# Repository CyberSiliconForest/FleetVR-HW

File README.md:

# FleetVR Hardware Design
## Abstract

## License
Most hardware designes are released under CERN OHL S v2.

Refer REUSE description for further information

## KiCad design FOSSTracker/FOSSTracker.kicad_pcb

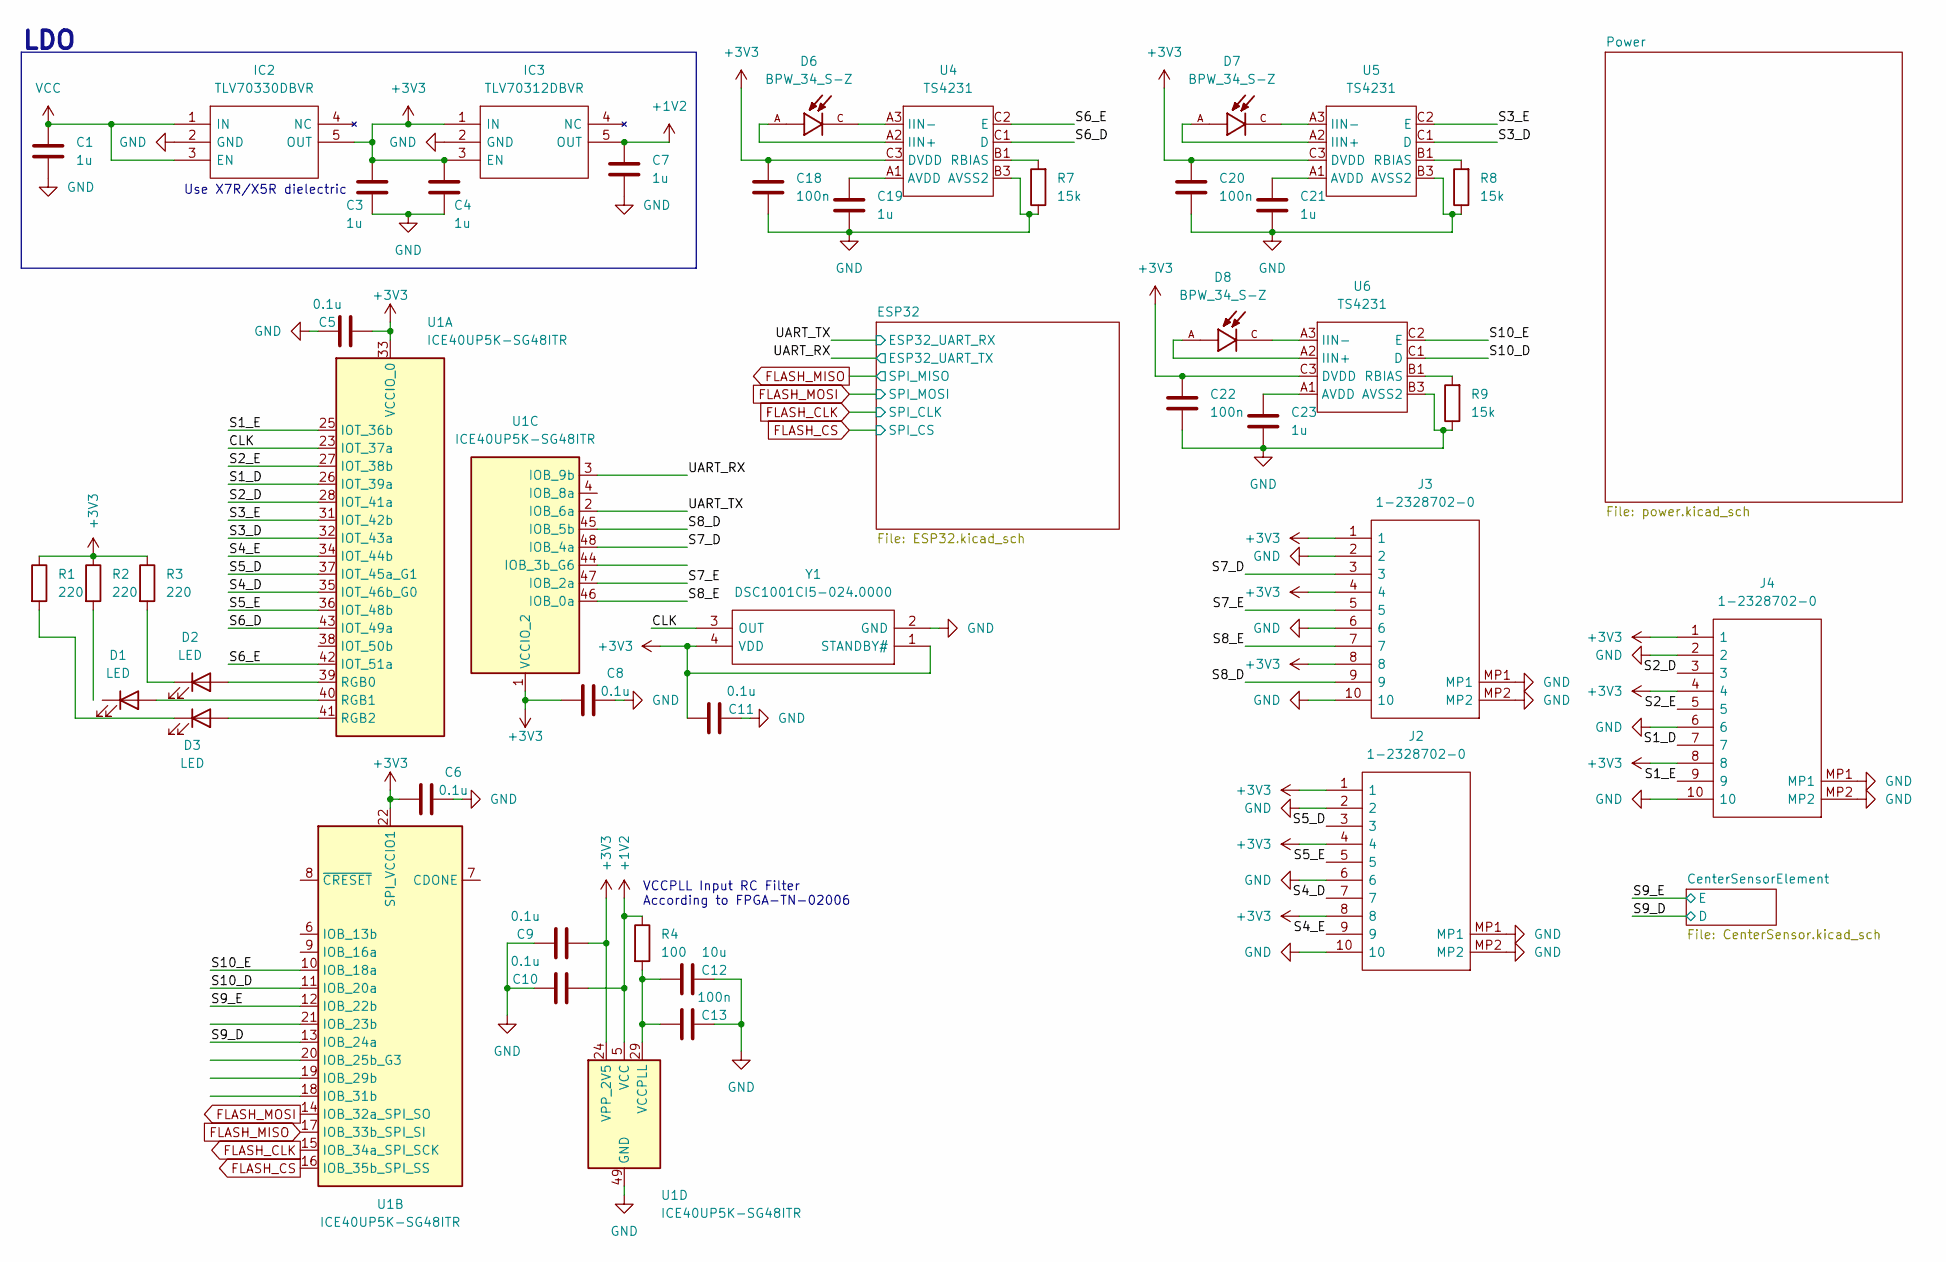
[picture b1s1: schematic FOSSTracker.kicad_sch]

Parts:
C1, C3, C4, C7, C19, C21, C23: 1u; C_0603_1608Metric
C5, C6, C8, C9, C10, C11: 0.1u; C_0603_1608Metric
C12: 10u; C_0603_1608Metric
C13, C18, C20, C22: 100n; C_0603_1608Metric
D1, D2, D3: LED; LED_0805_2012Metric_Pad1.15x1.40mm_HandSolder
D6, D7, D8: BPW_34_S-Z; DIO_BPW_34_S-Z; PARTREV 1.5
IC2: TLV70330DBVR; SOT95P280X145-5N; Mouser Part Number 595-TLV70330DBVR
IC3: TLV70312DBVR; SOT95P280X145-5N; Mouser Part Number 595-TLV70312DBVR
J2, J3, J4: 1-2328702-0; 123287020; Mouser Part Number 571-1-2328702-0
R1, R2, R3: 220; R_0603_1608Metric
R4: 100; R_0603_1608Metric
R7, R8, R9: 15k; R_0603_1608Metric
U1: ICE40UP5K-SG48ITR; QFN-48-1EP_7x7mm_P0.5mm_EP5.6x5.6mm
U4, U5, U6: TS4231; TS4231 WLCSP9
Y1: DSC1001CI5-024.0000; DSC1001CI50240000; Mouser Part Number 998-1001CI5-024.0000

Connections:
+1V2: C7.1, C10.1, IC3.5 (OUT), R4.1, U1.5 (VCC), U1.30 (VCC)
+3V3: C3.1, C4.1, C5.1, C6.1, C8.1, C9.1, C11.2, C18.1, C20.1, C22.1, IC2.5 (OUT), IC3.1 (IN), IC3.3 (EN), J2.1, J2.4, J2.8, J3.1, J3.4, J3.8, J4.1, J4.4, J4.8, R1.1, R2.1, R3.1, U1.1 (VCCIO_2), U1.22 (SPI_VCCIO1), U1.24 (VPP_2V5), U1.33 (VCCIO_0), U4.C3 (DVDD), U5.C3 (DVDD), U6.C3 (DVDD), Y1.1 (STANDBY#), Y1.4 (VDD); also elsewhere on the board
/CLK: U1.23 (IOT_37a), Y1.3 (OUT)
/S1_D: J4.7, U1.26 (IOT_39a)
/S1_E: J4.9, U1.25 (IOT_36b)
/S2_D: J4.3, U1.28 (IOT_41a)
/S2_E: J4.5, U1.27 (IOT_38b)
/S3_D: U1.32 (IOT_43a), U5.C1 (D)
/S3_E: U1.31 (IOT_42b), U5.C2 (E)
/S4_D: J2.7, U1.35 (IOT_46b_G0)
/S4_E: J2.9, U1.34 (IOT_44b)
/S5_D: J2.3, U1.37 (IOT_45a_G1)
/S5_E: J2.5, U1.36 (IOT_48b)
/S6_D: U1.43 (IOT_49a), U4.C1 (D)
/S6_E: U1.42 (IOT_51a), U4.C2 (E)
/S7_D: J3.3, U1.48 (IOB_4a)
/S7_E: J3.5, U1.47 (IOB_2a)
/S8_D: J3.9, U1.45 (IOB_5b)
/S8_E: J3.7, U1.46 (IOB_0a)
/S9_D: U1.13 (IOB_24a); also elsewhere on the board
/S9_E: U1.12 (IOB_22b); also elsewhere on the board
/S10_D: U1.11 (IOB_20a), U6.C1 (D)
/S10_E: U1.10 (IOB_18a), U6.C2 (E)
/UART_RX: U1.3 (IOB_9b); also elsewhere on the board
/UART_TX: U1.2 (IOB_6a); also elsewhere on the board
AVSS1: C1.2, C3.2, C4.2, C5.2, C6.2, C7.2, C8.2, C9.2, C10.2, C11.1, C12.1, C13.1, C18.2, C19.2, C20.2, C21.2, C22.2, C23.2, IC2.2 (GND), IC3.2 (GND), J2.2, J2.6, J2.10, J2.MP1, J2.MP2, J3.2, J3.6, J3.10, J3.MP1, J3.MP2, J4.2, J4.6, J4.10, J4.MP1, J4.MP2, R7.1, R8.1, R9.1, U1.49 (GND), U4.B2 (AVSS1), U4.B3 (AVSS2), U5.B2 (AVSS1), U5.B3 (AVSS2), U6.B2 (AVSS1), U6.B3 (AVSS2), Y1.2 (GND); also elsewhere on the board
FLASH_CLK: U1.15 (IOB_34a_SPI_SCK); also elsewhere on the board
FLASH_CS: U1.16 (IOB_35b_SPI_SS); also elsewhere on the board
FLASH_MISO: U1.17 (IOB_33b_SPI_SI); also elsewhere on the board
FLASH_MOSI: U1.14 (IOB_32a_SPI_SO); also elsewhere on the board
unnamed: C12.2, C13.2, R4.2, U1.29 (VCCPLL)
unnamed: C19.1, U4.A1 (AVDD)
unnamed: C21.1, U5.A1 (AVDD)
unnamed: C23.1, U6.A1 (AVDD)
unnamed: D1.2 (A), U1.40 (RGB1)
unnamed: D2.1 (K), R3.2
unnamed: D2.2 (A), U1.39 (RGB0)
unnamed: D3.1 (K), R1.2
unnamed: D3.2 (A), U1.41 (RGB2)
unnamed: D6.A, U4.A2 (IIN+)
unnamed: D6.C, U4.A3 (IIN-)
unnamed: D7.A, U5.A2 (IIN+)
unnamed: D7.C, U5.A3 (IIN-)
unnamed: D8.A, U6.A2 (IIN+)
unnamed: D8.C, U6.A3 (IIN-)
unnamed: R7.2, U4.B1 (RBIAS)
unnamed: R8.2, U5.B1 (RBIAS)
unnamed: R9.2, U6.B1 (RBIAS)
VCC: C1.1, IC2.1 (IN), IC2.3 (EN)

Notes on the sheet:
VCCPLL Input RC Filter According to FPGA-TN-02006
Use X7R/X5R dielectric
LDO

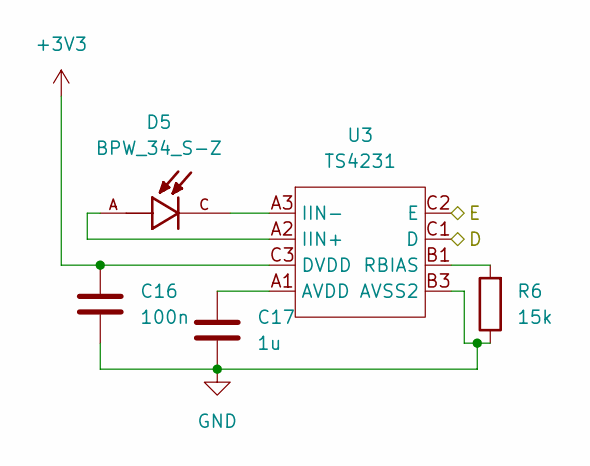
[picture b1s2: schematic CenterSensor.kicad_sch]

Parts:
C16: 100n; C_0603_1608Metric
C17: 1u; C_0603_1608Metric
D5: BPW_34_S-Z; DIO_BPW_34_S-Z; PARTREV 1.5
R6: 15k; R_0603_1608Metric
U3: TS4231; TS4231 WLCSP9

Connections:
+3V3: C16.1, U3.C3 (DVDD); also elsewhere on the board
/S9_D: U3.C1 (D); also elsewhere on the board
/S9_E: U3.C2 (E); also elsewhere on the board
AVSS1: C16.2, C17.2, R6.1, U3.B2 (AVSS1), U3.B3 (AVSS2); also elsewhere on the board
unnamed: C17.1, U3.A1 (AVDD)
unnamed: D5.A, U3.A2 (IIN+)
unnamed: D5.C, U3.A3 (IIN-)
unnamed: R6.2, U3.B1 (RBIAS)

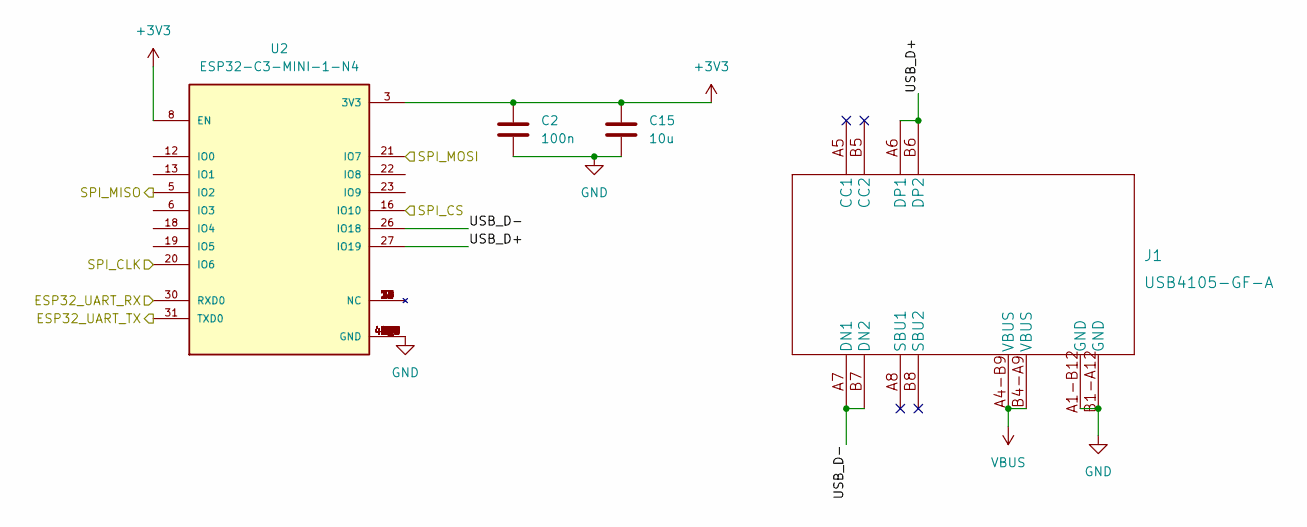
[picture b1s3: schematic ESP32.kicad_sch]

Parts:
C2: 100n; C_0603_1608Metric
C15: 10u; C_0603_1608Metric
J1: USB4105-GF-A
U2: ESP32-C3-MINI-1-N4; XCVR_ESP32-C3-MINI-1-N4; PARTREV v1.0

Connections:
+3V3: C2.1, C15.1, U2.3 (3V3), U2.8 (EN); also elsewhere on the board
/ESP32/USB_D+: J1.A6 (DP1), J1.B6 (DP2), U2.27 (IO19)
/ESP32/USB_D-: J1.A7 (DN1), J1.B7 (DN2), U2.26 (IO18)
/UART_RX: U2.31 (TXD0); also elsewhere on the board
/UART_TX: U2.30 (RXD0); also elsewhere on the board
AVSS1: C2.2, C15.2, J1.A1-B12 (GND), J1.B1-A12 (GND), U2.1 (GND), U2.2 (GND), U2.11 (GND), U2.14 (GND), U2.36 (GND), U2.37 (GND), U2.38 (GND), U2.39 (GND), U2.40 (GND), U2.41 (GND), U2.42 (GND), U2.43 (GND), U2.44 (GND), U2.45 (GND), U2.46 (GND), U2.47 (GND), U2.48 (GND), U2.49_1 (GND), U2.49_2 (GND), U2.49_3 (GND), U2.49_4 (GND), U2.49_5 (GND), U2.49_6 (GND), U2.49_7 (GND), U2.49_8 (GND), U2.49_9 (GND), U2.50 (GND), U2.51 (GND), U2.52 (GND), U2.53 (GND); also elsewhere on the board
FLASH_CLK: U2.20 (IO6); also elsewhere on the board
FLASH_CS: U2.16 (IO10); also elsewhere on the board
FLASH_MISO: U2.5 (IO2); also elsewhere on the board
FLASH_MOSI: U2.21 (IO7); also elsewhere on the board
VBUS: J1.A4-B9 (VBUS), J1.B4-A9 (VBUS)

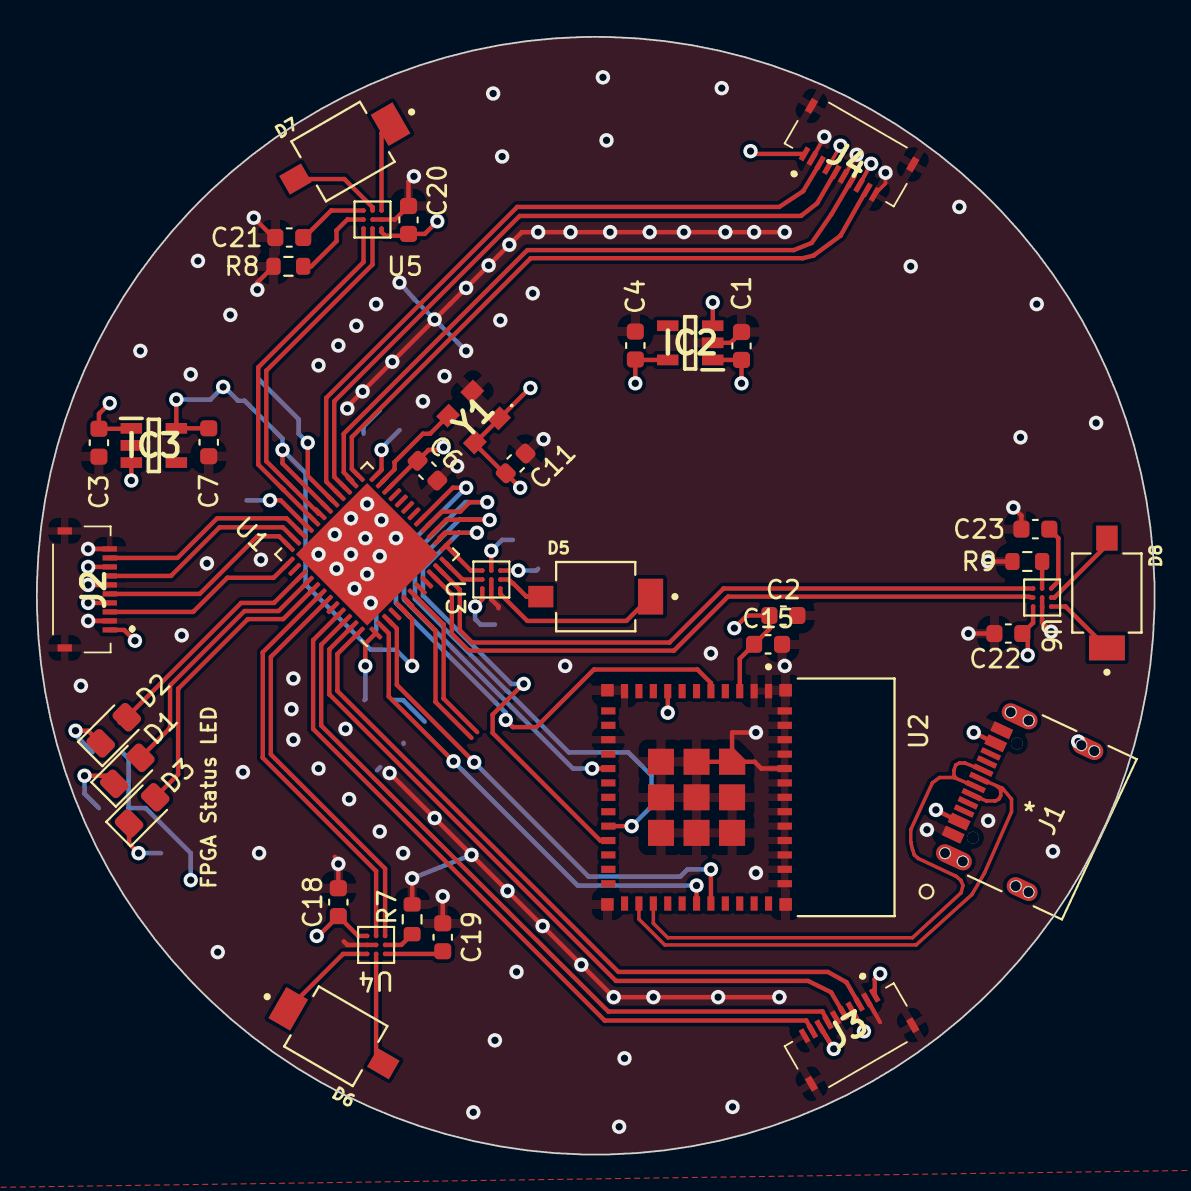
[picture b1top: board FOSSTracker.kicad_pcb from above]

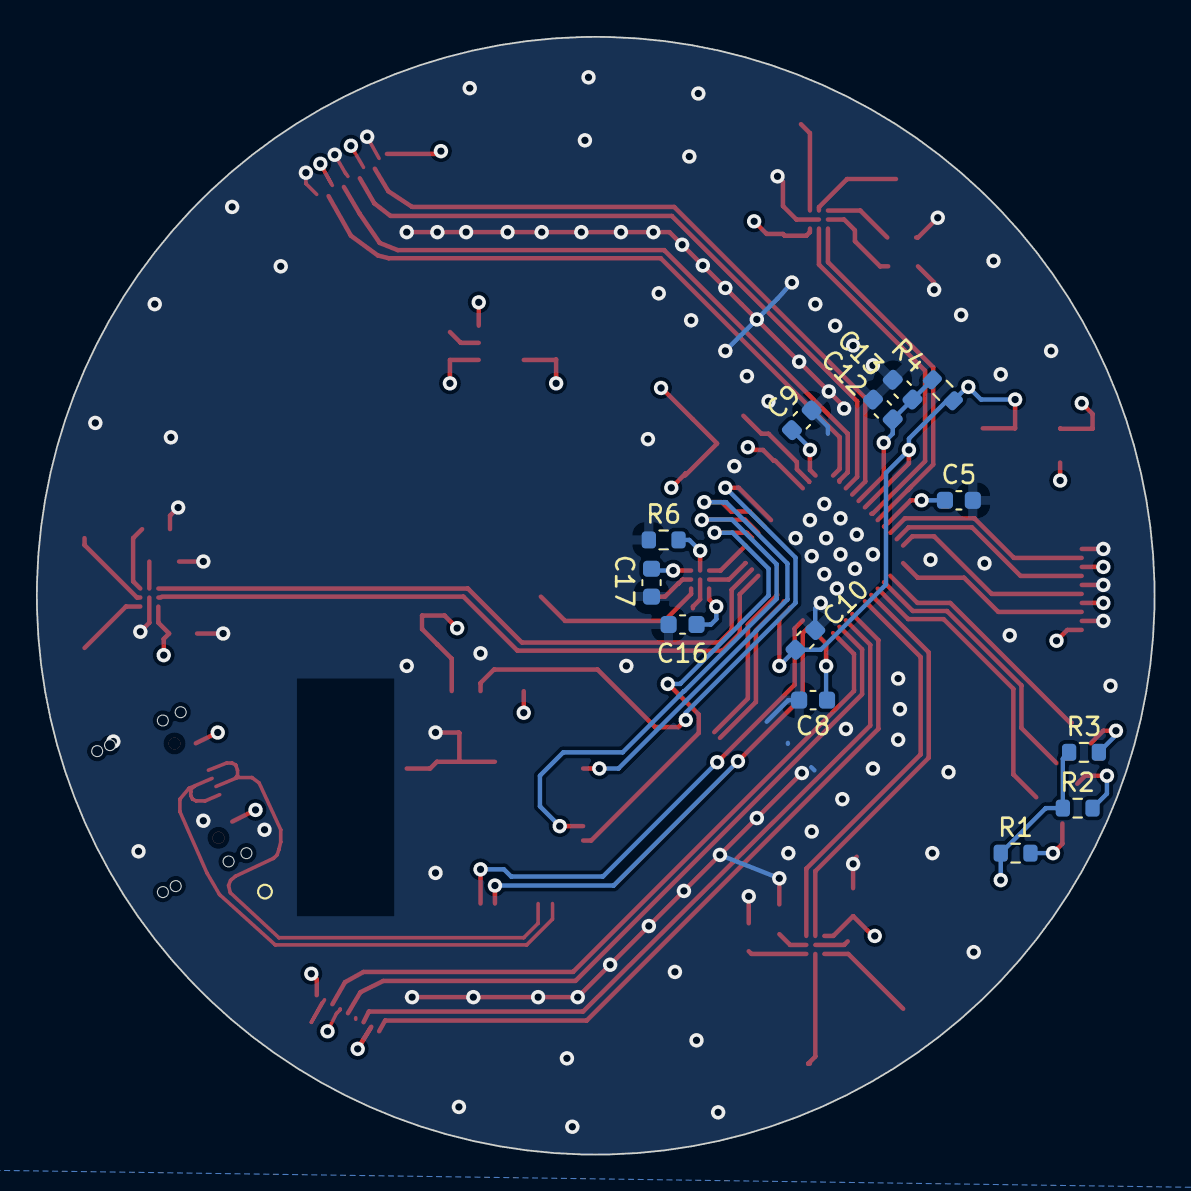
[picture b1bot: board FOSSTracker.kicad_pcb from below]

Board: 4 copper layers, 62.1 x 62.1 mm, 50 parts (13 on the bottom side), 56 nets.

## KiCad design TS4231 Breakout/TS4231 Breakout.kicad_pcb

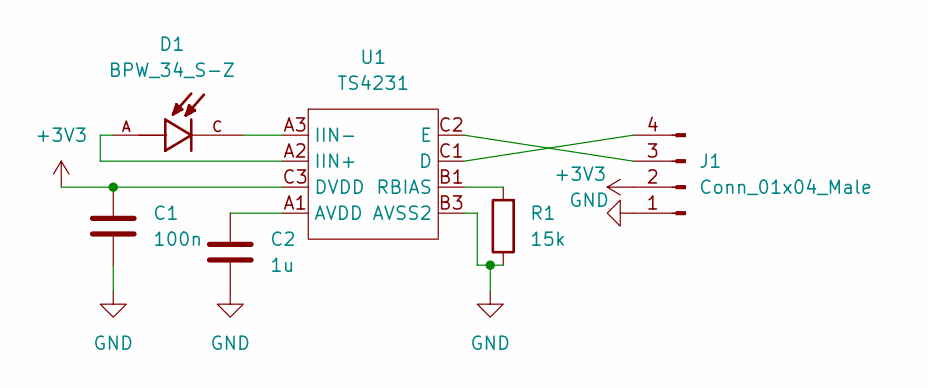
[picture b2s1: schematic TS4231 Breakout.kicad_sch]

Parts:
C1: 100n; C_0603_1608Metric_Pad1.08x0.95mm_HandSolder
C2: 1u; C_0603_1608Metric_Pad1.08x0.95mm_HandSolder
D1: BPW_34_S-Z; DIO_BPW_34_S-Z; PARTREV 1.5
J1: Conn_01x04_Male; PinHeader_1x04_P2.54mm_Horizontal
R1: 15k; R_0603_1608Metric_Pad0.98x0.95mm_HandSolder
U1: TS4231; TS4231 WLCSP9

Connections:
+3V3: C1.1, J1.2, U1.C3 (DVDD)
AVSS1: C1.2, C2.2, J1.1, R1.1, U1.B2 (AVSS1), U1.B3 (AVSS2)
unnamed: C2.1, U1.A1 (AVDD)
unnamed: D1.A, U1.A2 (IIN+)
unnamed: D1.C, U1.A3 (IIN-)
unnamed: J1.3, U1.C2 (E)
unnamed: J1.4, U1.C1 (D)
unnamed: R1.2, U1.B1 (RBIAS)

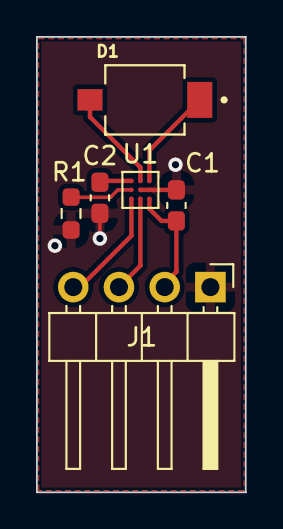
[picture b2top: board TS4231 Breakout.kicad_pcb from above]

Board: 2 copper layers, 11.6 x 25.3 mm, 6 parts (0 on the bottom side), 8 nets.

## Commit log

2022-05-21 Add licenses
2022-05-21 Commit README.md
2022-05-21 Add gitignore
2022-05-21 TS423l Breakout Board Schematic and PCB for Development
2022-05-22 Tracker Hardware (Work in progress)

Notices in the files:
parts and their libraries:
Copyright 2021 Accelerated Designs. All rights reserved.
